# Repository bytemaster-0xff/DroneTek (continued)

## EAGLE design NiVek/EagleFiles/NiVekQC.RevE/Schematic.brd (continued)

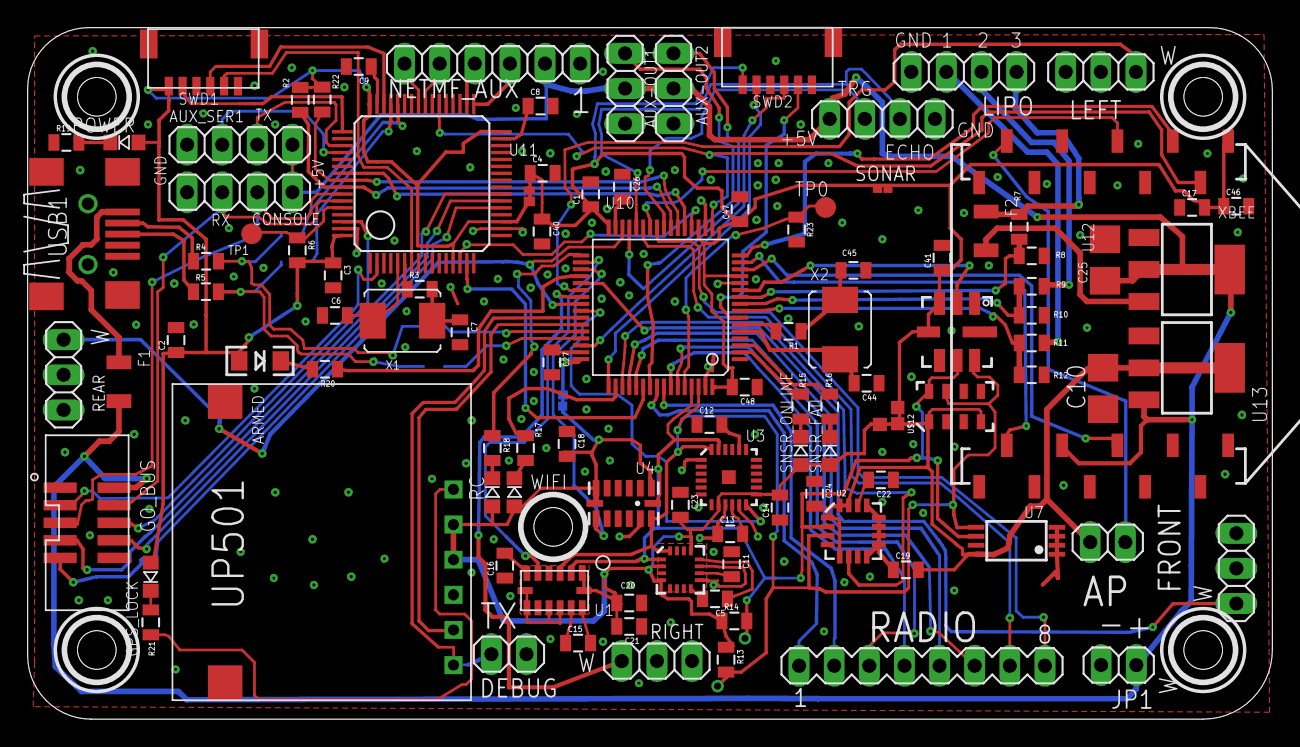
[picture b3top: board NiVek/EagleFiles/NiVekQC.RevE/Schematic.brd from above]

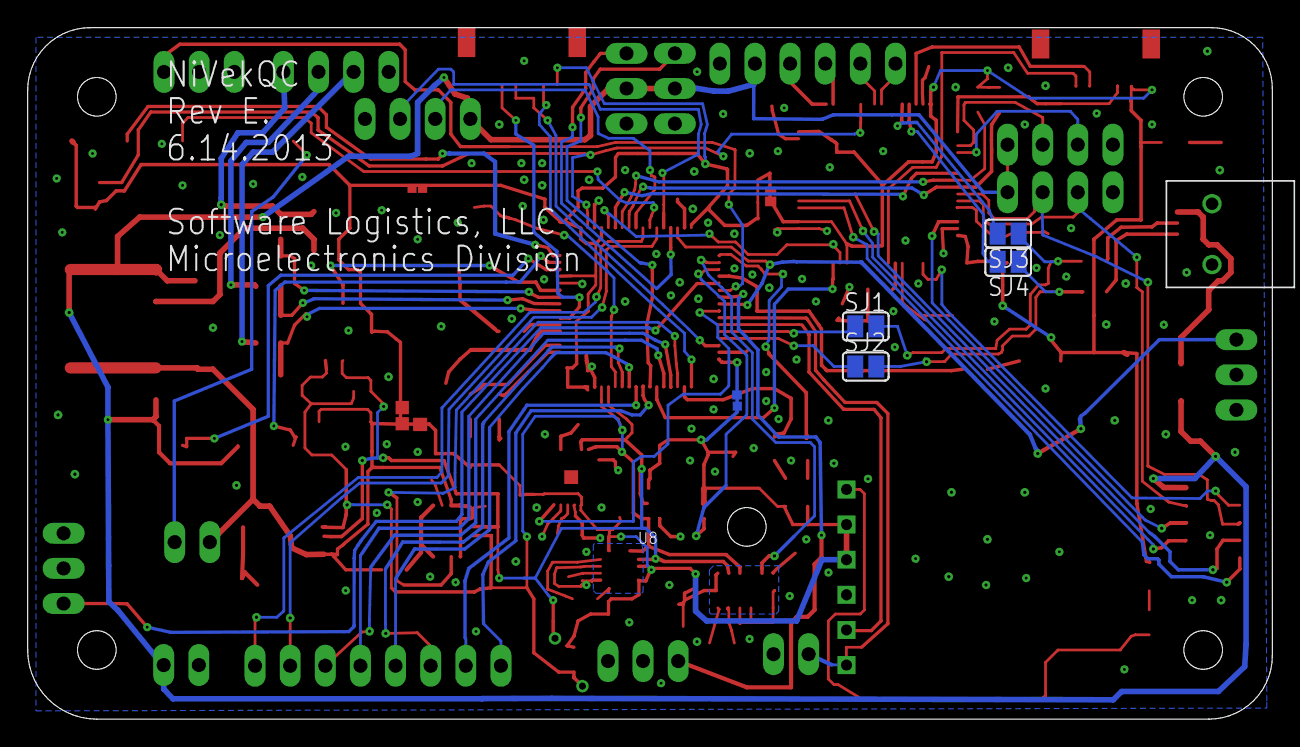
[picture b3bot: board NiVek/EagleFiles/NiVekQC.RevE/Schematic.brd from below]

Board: 2 copper layers, 90.0 x 50.0 mm, 107 parts (4 on the bottom side), 108 nets.

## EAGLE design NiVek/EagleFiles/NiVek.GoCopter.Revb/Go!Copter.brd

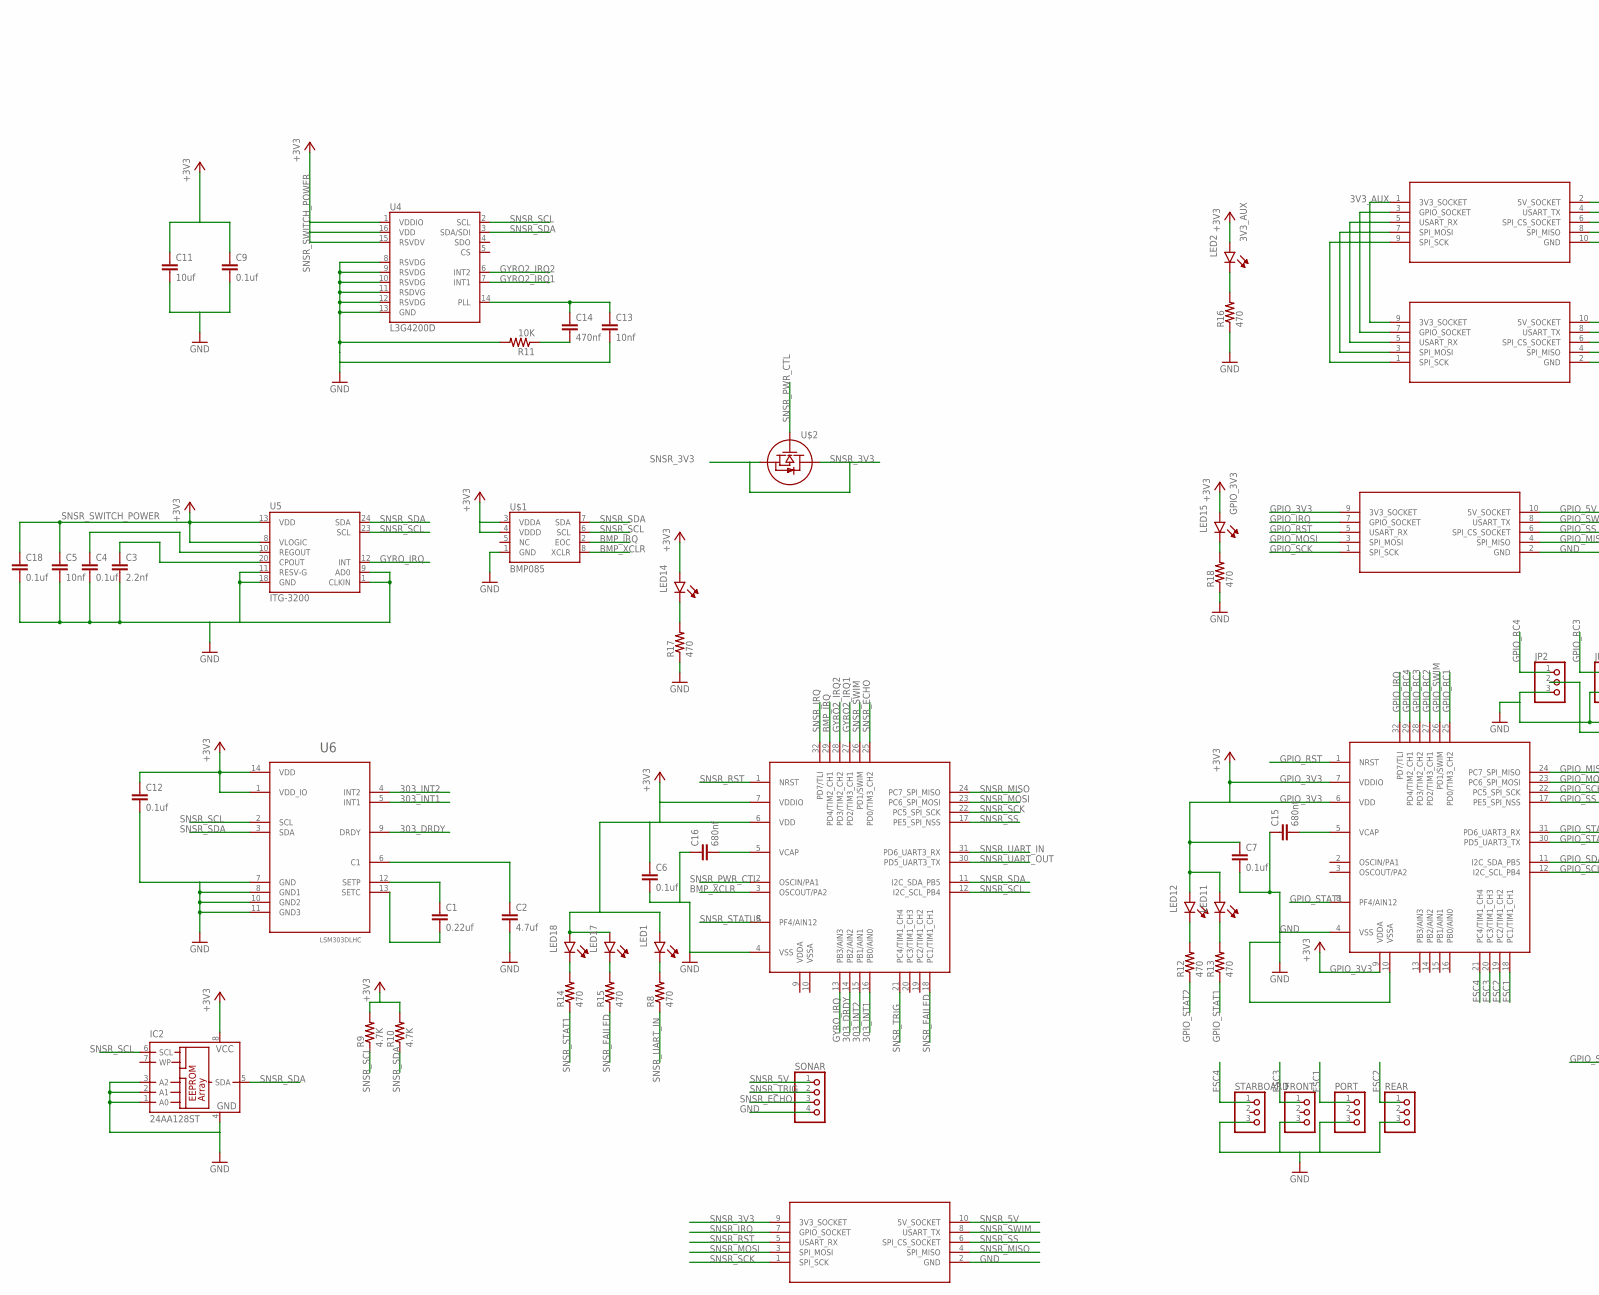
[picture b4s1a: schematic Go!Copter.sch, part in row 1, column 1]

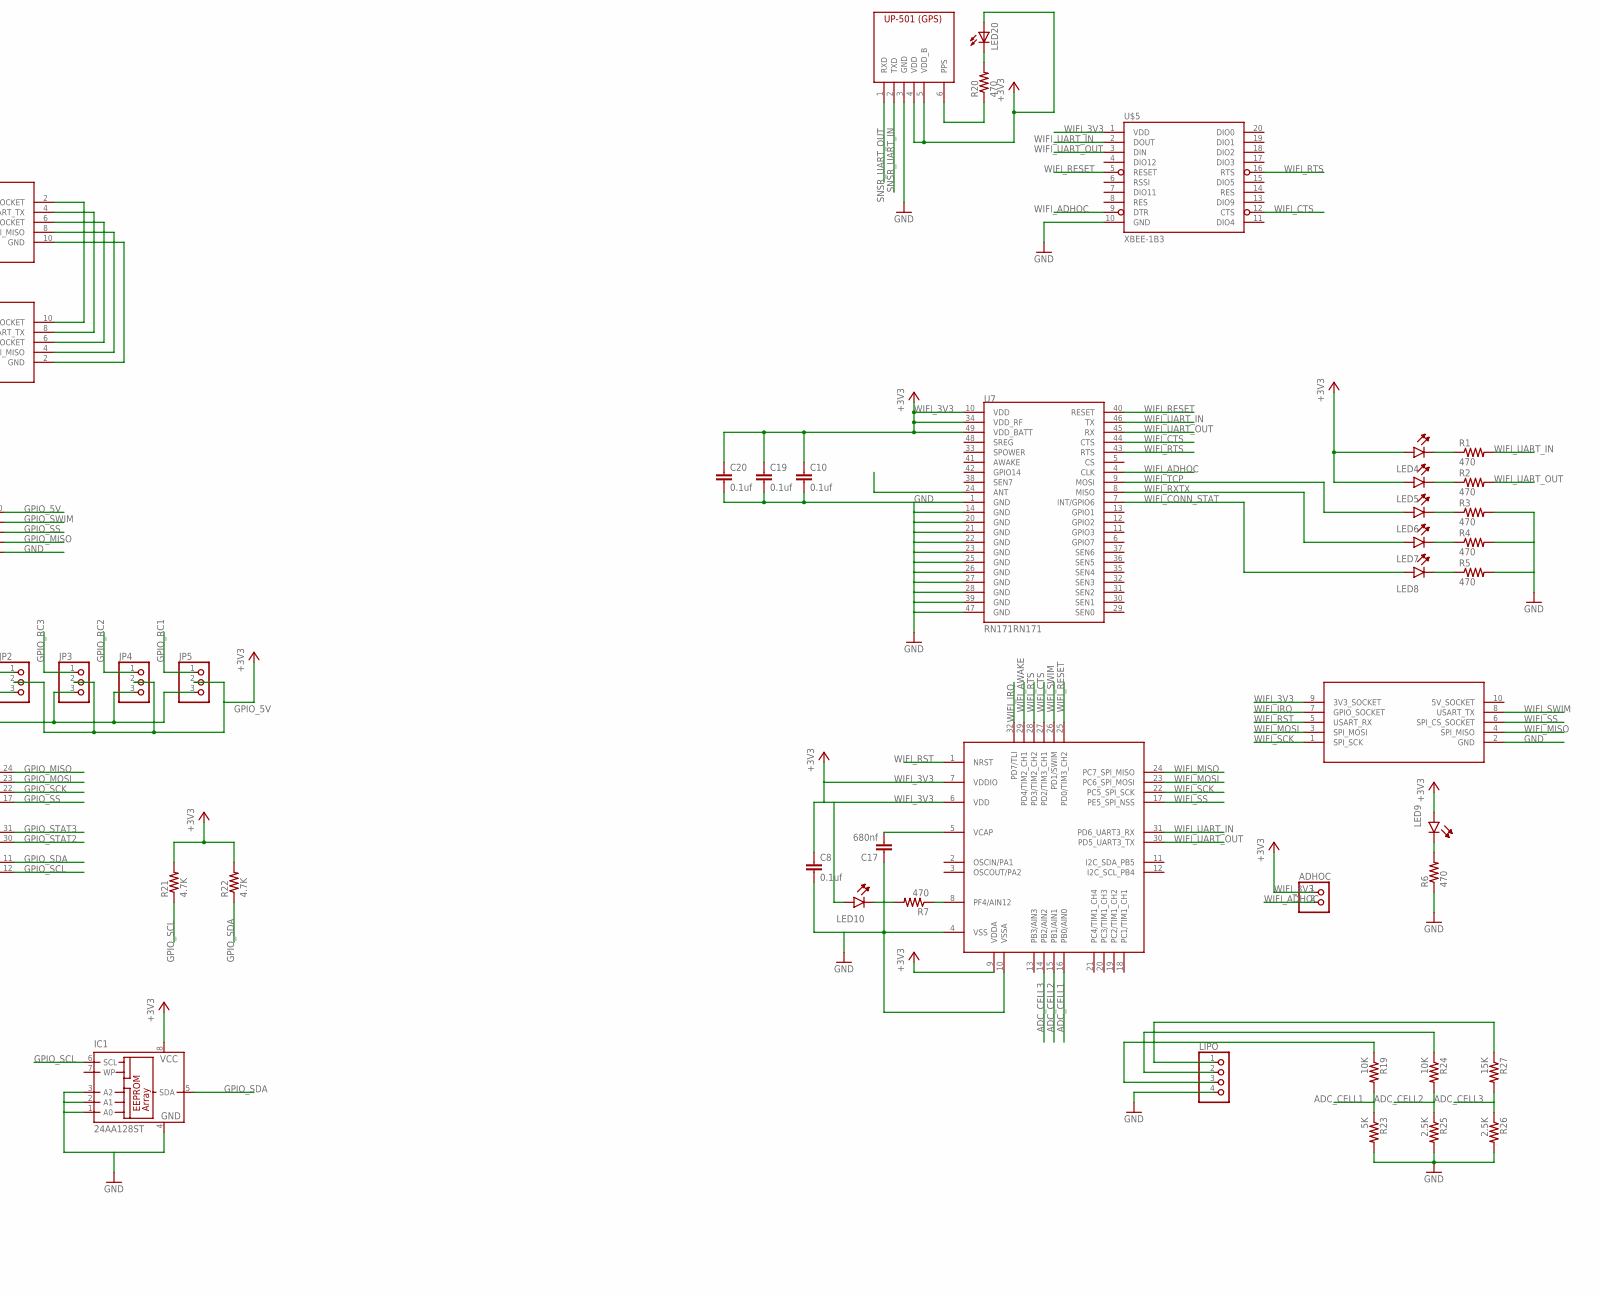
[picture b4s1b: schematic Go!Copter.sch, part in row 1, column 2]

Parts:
ADHOC: PINHD-1X2; 1X02
C1: 0.22uf; 0805
C2: 4.7uf; 0805
C3: 2.2nf; 0805
C4, C6, C7, C8, C9, C10, C12, C18, C19, C20: 0.1uf; 0805
C5, C13: 10nf; 0805
C11: 10uf; 0805
C14: 470nf; 0805
C15, C16, C17: 680nf; 0805
FRONT: PINHD-1X3; 1X03
IC1, IC2: 24AA128ST; TSSOP8; MPN 24AA128-I/ST
JP2, JP3, JP4, JP5: PINHD-1X3; 1X03
LED1, LED2, LED4, LED5, LED6, LED7, LED8, LED9, LED10, LED11, LED12, LED14, LED15, LED17, LED18: SMD_LED0805; LED0805
LED20: LEDCHIPLED_0805; CHIPLED_0805
LIPO: PINHD-1X4; 1X04
PORT: PINHD-1X3; 1X03
R1, R2, R3, R4, R5, R6, R7, R8, R12, R13, R14, R15, R16, R17, R18, R20: 470; 0805
R9, R10, R21, R22: 4.7K; 0805
R11, R19, R24: 10K; 0805
R23: 5K; 0805
R25, R26: 2.5K; 0805
R27: 15K; 0805
REAR: PINHD-1X3; 1X03
SONAR: PINHD-1X4; 1X04
STARBOARD: PINHD-1X3; 1X03
U1, U2, U3: STM8S207K6; LQFP32
U4: L3G4200D; LGA16-4X4
U5: ITG-3200; QFN-24
U6: LSM303DLHC; LGA3X5X1-14L
U7: RN171RN171; RN171
U$1: BMP085
U$2: MOSFET-BSS138; SOT-23
U$3, U$4, U$7, U$8: GO!BUS-FEMALE; PIN2ROW_0.05"
U$5: XBEE-1B3; XBEE-SMD
U$6: UP501; UP-501
U$9: GO!BUS; PIN2ROW_0.05"

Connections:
3V3_AUX: LED2.P$1 (A), U$8.9 (3V3_SOCKET), U$9.1 (3V3_SOCKET)
5V_AUX: U$8.10 (5V_SOCKET), U$9.2 (5V_SOCKET)
5V_SOCKET: U$4.10 (5V_SOCKET)
303_DRDY: U1.14 (PB2/AIN2), U6.9 (DRDY)
303_INT1: U1.16 (PB0/AIN0), U6.5 (INT1)
303_INT2: U1.15 (PB1/AIN1), U6.4 (INT2)
+3V3: U3.9 (VDDA)
ADC_CELL1: R19.2, R23.1, U3.16 (PB0/AIN0)
ADC_CELL2: R24.2, R25.1, U3.15 (PB1/AIN1)
ADC_CELL3: R26.1, R27.2, U3.14 (PB2/AIN2)
ANTENNA: U7.24 (ANT)
BMP_IRQ: U1.29 (PD4/TIM2_CH1), U$1.2 (EOC)
BMP_XCLR: U1.3 (OSCOUT/PA2), U$1.8 (XCLR)
ESC1: PORT.1, U2.18 (PC1/TIM1_CH1)
ESC2: REAR.1, U2.19 (PC2/TIM1_CH2)
ESC3: FRONT.1, U2.20 (PC3/TIM1_CH3)
ESC4: STARBOARD.1, U2.21 (PC4/TIM1_CH4)
GND: C2.2, C3.2, C4.2, C5.2, C6.2, C7.2, C8.2, C9.2, C10.2, C11.2, C12.2, C13.2, C15.1, C16.1, C17.1, C18.2, C19.2, C20.2, FRONT.3, IC1.1 (A0), IC1.2 (A1), IC1.3 (A2), IC1.4 (GND), IC2.1 (A0), IC2.2 (A1), IC2.3 (A2), IC2.4 (GND), JP2.3, JP3.3, JP4.3, JP5.3, LIPO.4, PORT.3, R3.2, R4.2, R5.2, R6.1, R11.2, R16.1, R17.1, R18.1, R23.2, R25.2, R26.2, REAR.3, SONAR.4, STARBOARD.3, U1.4 (VSS), U2.4 (VSS), U2.10 (VSSA), U3.4 (VSS), U3.10 (VSSA), U4.8 (RSVDG), U4.9 (RSVDG), U4.10 (RSVDG), U4.11 (RSDVG), U4.12 (RSVDG), U4.13 (GND), U5.1 (CLKIN), U5.9 (AD0), U5.11 (RESV-G), U5.18 (GND), U6.7 (GND), U6.8 (GND1), U6.10 (GND2), U6.11 (GND3), U7.1 (GND), U7.14 (GND), U7.20 (GND), U7.21 (GND), U7.22 (GND), U7.23 (GND), U7.25 (GND), U7.26 (GND), U7.27 (GND), U7.28 (GND), U7.39 (GND), U7.47 (GND), U$1.1 (GND), U$3.2 (GND), U$4.2 (GND), U$5.10 (GND), U$6.3 (GND), U$7.2 (GND), U$8.2 (GND), U$9.10 (GND)
GPIO_3V3: C7.1, IC1.8 (VCC), LED11.P$1 (A), LED12.P$1 (A), LED15.P$1 (A), R21.2, R22.2, U2.6 (VDD), U2.7 (VDDIO), U2.9 (VDDA), U$3.9 (3V3_SOCKET)
GPIO_5V: JP2.2, JP3.2, JP4.2, JP5.2, U$3.10 (5V_SOCKET)
GPIO_IRQ: U2.32 (PD7/TLI), U$3.7 (GPIO_SOCKET)
GPIO_MISO: U2.24 (PC7_SPI_MISO), U$3.4 (SPI_MISO)
GPIO_MOSI: U2.23 (PC6_SPI_MOSI), U$3.3 (SPI_MOSI)
GPIO_RC1: JP5.1, U2.25 (PD0/TIM3_CH2)
GPIO_RC2: JP4.1, U2.27 (PD2/TIM3_CH1)
GPIO_RC3: JP3.1, U2.28 (PD3/TIM2_CH2)
GPIO_RC4: JP2.1, U2.29 (PD4/TIM2_CH1)
GPIO_RST: U2.1 (NRST), U$3.5 (USART_RX)
GPIO_SCK: U2.22 (PC5_SPI_SCK), U$3.1 (SPI_SCK)
GPIO_SCL: IC1.6 (SCL), R21.1, U2.12 (I2C_SCL_PB4)
GPIO_SDA: IC1.5 (SDA), R22.1, U2.11 (I2C_SDA_PB5)
GPIO_SS: U2.17 (PE5_SPI_NSS), U$3.6 (SPI_CS_SOCKET)
GPIO_STAT1: R13.1, U2.8 (PF4/AIN12)
GPIO_STAT2: R12.1, U2.30 (PD5_UART3_TX)
GPIO_STAT3: U2.31 (PD6_UART3_RX)
GPIO_SWIM: U2.26 (PD1/SWIM), U$3.8 (USART_TX)
GYRO2_IRQ1: U1.27 (PD2/TIM3_CH1), U4.7 (INT1)
GYRO2_IRQ2: U1.28 (PD3/TIM2_CH2), U4.6 (INT2)
GYRO_IRQ: U1.13 (PB3/AIN3), U5.12 (INT)
unnamed: LED18.C, R14.2
unnamed: LED1.C, R8.2
unnamed: C4.1, U5.10 (REGOUT)
unnamed: C3.1, U5.20 (CPOUT)
unnamed: LED4.C, R1.1
unnamed: C1.1, U6.12 (SETP)
unnamed: C1.2, U6.13 (SETC)
unnamed: C2.1, U6.6 (C1)
unnamed: LED5.C, R2.1
unnamed: LED6.C, R3.1
unnamed: LED7.C, R4.1
unnamed: LED8.C, R5.1
unnamed: LED9.C, R6.2
unnamed: LED10.C, R7.2
unnamed: R7.1, U3.8 (PF4/AIN12)
unnamed: LED17.C, R15.2
unnamed: LED15.C, R18.2
unnamed: LED2.C, R16.2
unnamed: LED12.C, R12.2
unnamed: LED11.C, R13.2
unnamed: U$8.7 (GPIO_SOCKET), U$9.3 (GPIO_SOCKET)
unnamed: LED14.C, R17.2
unnamed: U$8.5 (USART_RX), U$9.5 (USART_RX)
unnamed: U$8.3 (SPI_MOSI), U$9.7 (SPI_MOSI)
unnamed: R20.1, U$6.6 (PPS)
unnamed: C15.2, U2.5 (VCAP)
unnamed: U$8.1 (SPI_SCK), U$9.9 (SPI_SCK)
unnamed: LED20.C, R20.2
unnamed: C16.2, U1.5 (VCAP)
unnamed: C17.2, U3.5 (VCAP)
unnamed: C14.2, R11.1
unnamed: U$8.8 (USART_TX), U$9.4 (USART_TX)
unnamed: U$8.6 (SPI_CS_SOCKET), U$9.6 (SPI_CS_SOCKET)
unnamed: U$8.4 (SPI_MISO), U$9.8 (SPI_MISO)
unnamed: C13.1, C14.1, U4.14 (PLL)
unnamed: LIPO.3, R19.1
unnamed: LIPO.2, R24.1
unnamed: LIPO.1, R27.1
SNSR_3V3: C6.1, IC2.8 (VCC), LED1.P$1 (A), LED14.P$1 (A), LED17.P$1 (A), LED18.P$1 (A), LED20.A, R9.2, R10.2, U1.6 (VDD), U1.7 (VDDIO), U$2.BOTTOM_RIGHT (S), U$2.TOP (D), U$6.4 (VDD), U$6.5 (VDD_B), U$7.9 (3V3_SOCKET)
SNSR_5V: SONAR.1, U$7.10 (5V_SOCKET)
SNSR_ECHO: SONAR.3, U1.25 (PD0/TIM3_CH2)
SNSR_FAILED: R15.1, U1.18 (PC1/TIM1_CH1)
SNSR_IRQ: U1.32 (PD7/TLI), U$7.7 (GPIO_SOCKET)
SNSR_MISO: U1.24 (PC7_SPI_MISO), U$7.4 (SPI_MISO)
SNSR_MOSI: U1.23 (PC6_SPI_MOSI), U$7.3 (SPI_MOSI)
SNSR_PWR_CTL: U1.2 (OSCIN/PA1), U$2.BOTTOM_LEFT (G)
SNSR_RST: U1.1 (NRST), U$7.5 (USART_RX)
SNSR_SCK: U1.22 (PC5_SPI_SCK), U$7.1 (SPI_SCK)
SNSR_SCL: IC2.6 (SCL), R9.1, U1.12 (I2C_SCL_PB4), U4.2 (SCL), U5.23 (SCL), U6.2 (SCL), U$1.6 (SCL)
SNSR_SDA: IC2.5 (SDA), R10.1, U1.11 (I2C_SDA_PB5), U4.3 (SDA/SDI), U5.24 (SDA), U6.3 (SDA), U$1.7 (SDA)
SNSR_SS: U1.17 (PE5_SPI_NSS), U$7.6 (SPI_CS_SOCKET)
SNSR_STAT1: R14.1
SNSR_STATUS: U1.8 (PF4/AIN12)
SNSR_SWIM: U1.26 (PD1/SWIM), U$7.8 (USART_TX)
SNSR_SWITCH_POWER: C5.1, C9.1, C11.1, C12.1, C18.1, U4.1 (VDDIO), U4.15 (RSVDV), U4.16 (VDD), U5.8 (VLOGIC), U5.13 (VDD), U6.1 (VDD_IO), U6.14 (VDD), U$1.3 (VDDA), U$1.4 (VDDD)
SNSR_TRIG: SONAR.2, U1.21 (PC4/TIM1_CH4)
SNSR_UART_IN: R8.1, U1.31 (PD6_UART3_RX), U$6.2 (TXD)
SNSR_UART_OUT: U1.30 (PD5_UART3_TX), U$6.1 (RXD)
WIFI_3V3: ADHOC.1, C8.1, C10.1, C19.1, C20.1, LED4.P$1 (A), LED5.P$1 (A), LED9.P$1 (A), LED10.P$1 (A), U3.6 (VDD), U3.7 (VDDIO), U7.10 (VDD), U7.34 (VDD_RF), U7.49 (VDD_BATT), U$4.9 (3V3_SOCKET), U$5.1 (VDD)
WIFI_ADHOC: ADHOC.2, U7.4 (CLK), U$5.9 (DTR)
WIFI_AWAKE: U3.29 (PD4/TIM2_CH1)
WIFI_CONN_STAT: LED8.P$1 (A), U7.7 (INT/GPIO6)
WIFI_CTS: U3.27 (PD2/TIM3_CH1), U7.44 (CTS), U$5.12 (CTS)
WIFI_IRQ: U3.32 (PD7/TLI), U$4.7 (GPIO_SOCKET)
WIFI_MISO: U3.24 (PC7_SPI_MISO), U$4.4 (SPI_MISO)
WIFI_MOSI: U3.23 (PC6_SPI_MOSI), U$4.3 (SPI_MOSI)
WIFI_RESET: U3.25 (PD0/TIM3_CH2), U7.40 (RESET), U$5.5 (RESET)
WIFI_RST: U3.1 (NRST), U$4.5 (USART_RX)
WIFI_RTS: U3.28 (PD3/TIM2_CH2), U7.43 (RTS), U$5.16 (RTS)
WIFI_RXTX: LED7.P$1 (A), U7.8 (MISO)
WIFI_SCK: U3.22 (PC5_SPI_SCK), U$4.1 (SPI_SCK)
WIFI_SS: U3.17 (PE5_SPI_NSS), U$4.6 (SPI_CS_SOCKET)
WIFI_SWIM: U3.26 (PD1/SWIM), U$4.8 (USART_TX)
WIFI_TCP: LED6.P$1 (A), U7.9 (MOSI)
WIFI_UART_IN: R1.2, U3.31 (PD6_UART3_RX), U7.46 (TX), U$5.2 (DOUT)
WIFI_UART_OUT: R2.2, U3.30 (PD5_UART3_TX), U7.45 (RX), U$5.3 (DIN)

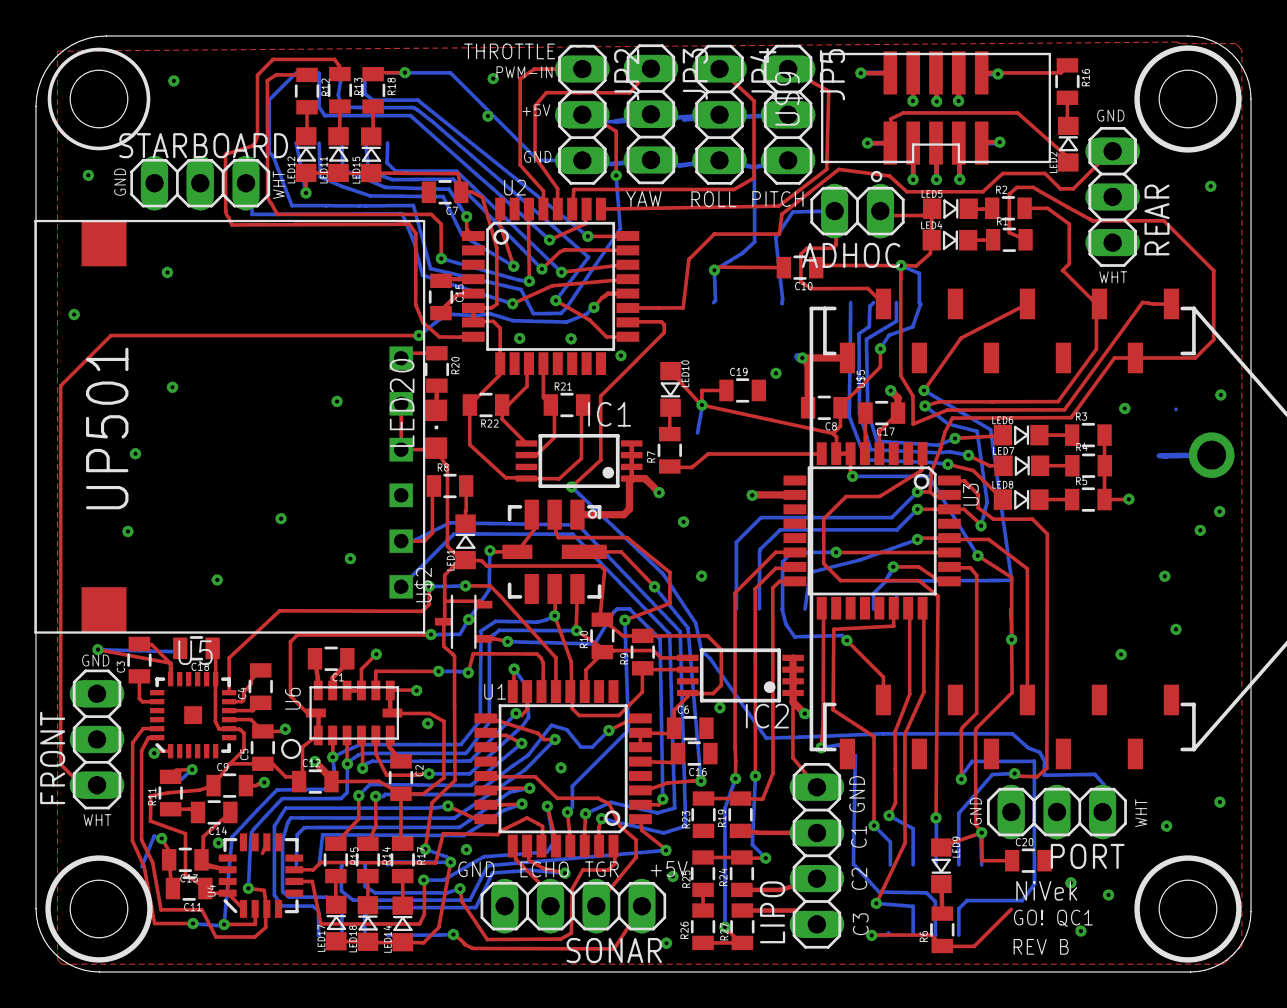
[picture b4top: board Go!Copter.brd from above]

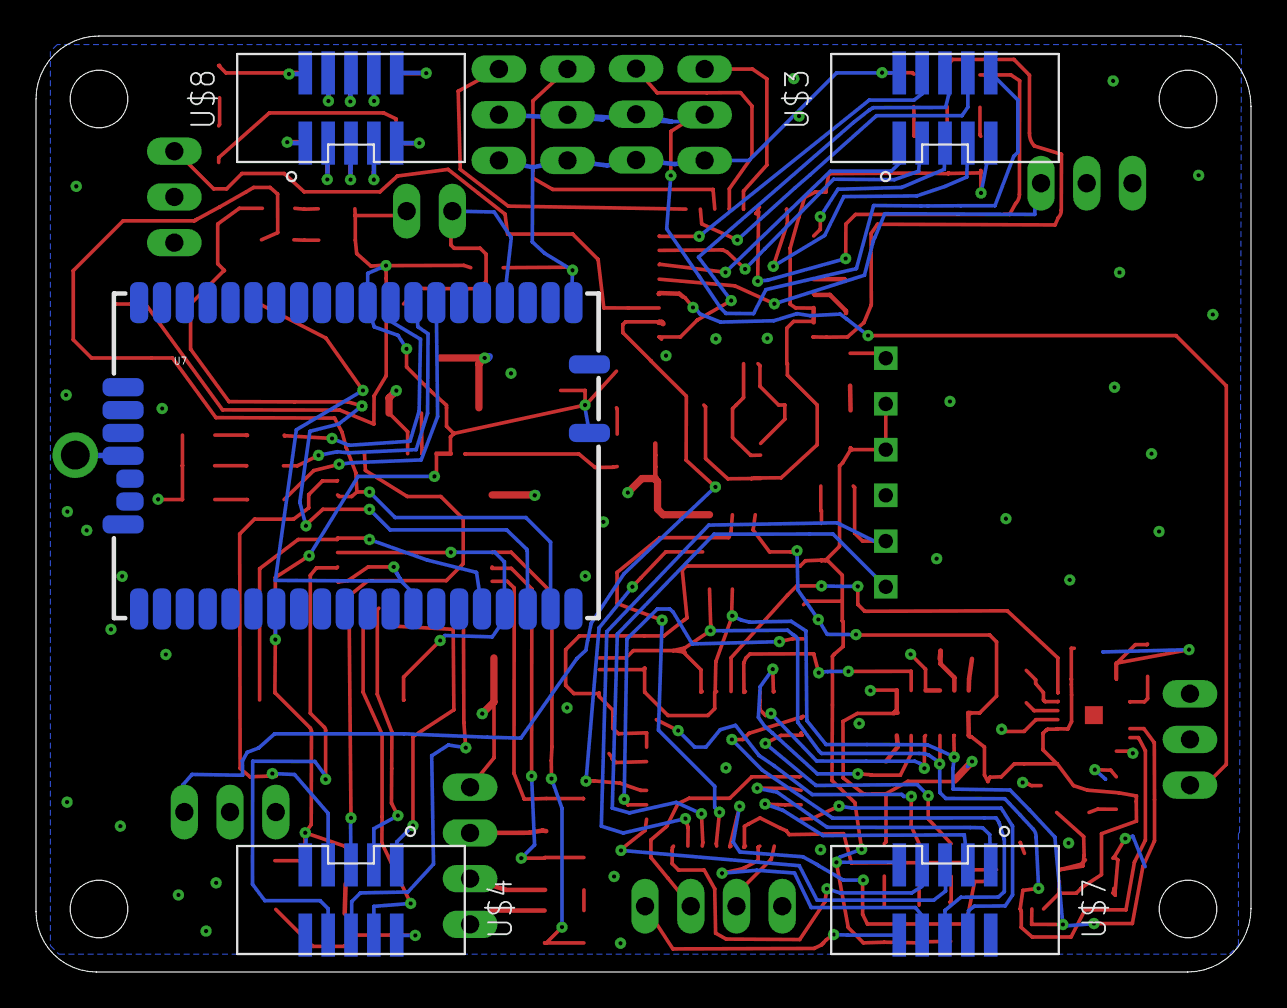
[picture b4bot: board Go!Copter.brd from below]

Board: 2 copper layers, 67.5 x 52.0 mm, 92 parts (5 on the bottom side), 108 nets.

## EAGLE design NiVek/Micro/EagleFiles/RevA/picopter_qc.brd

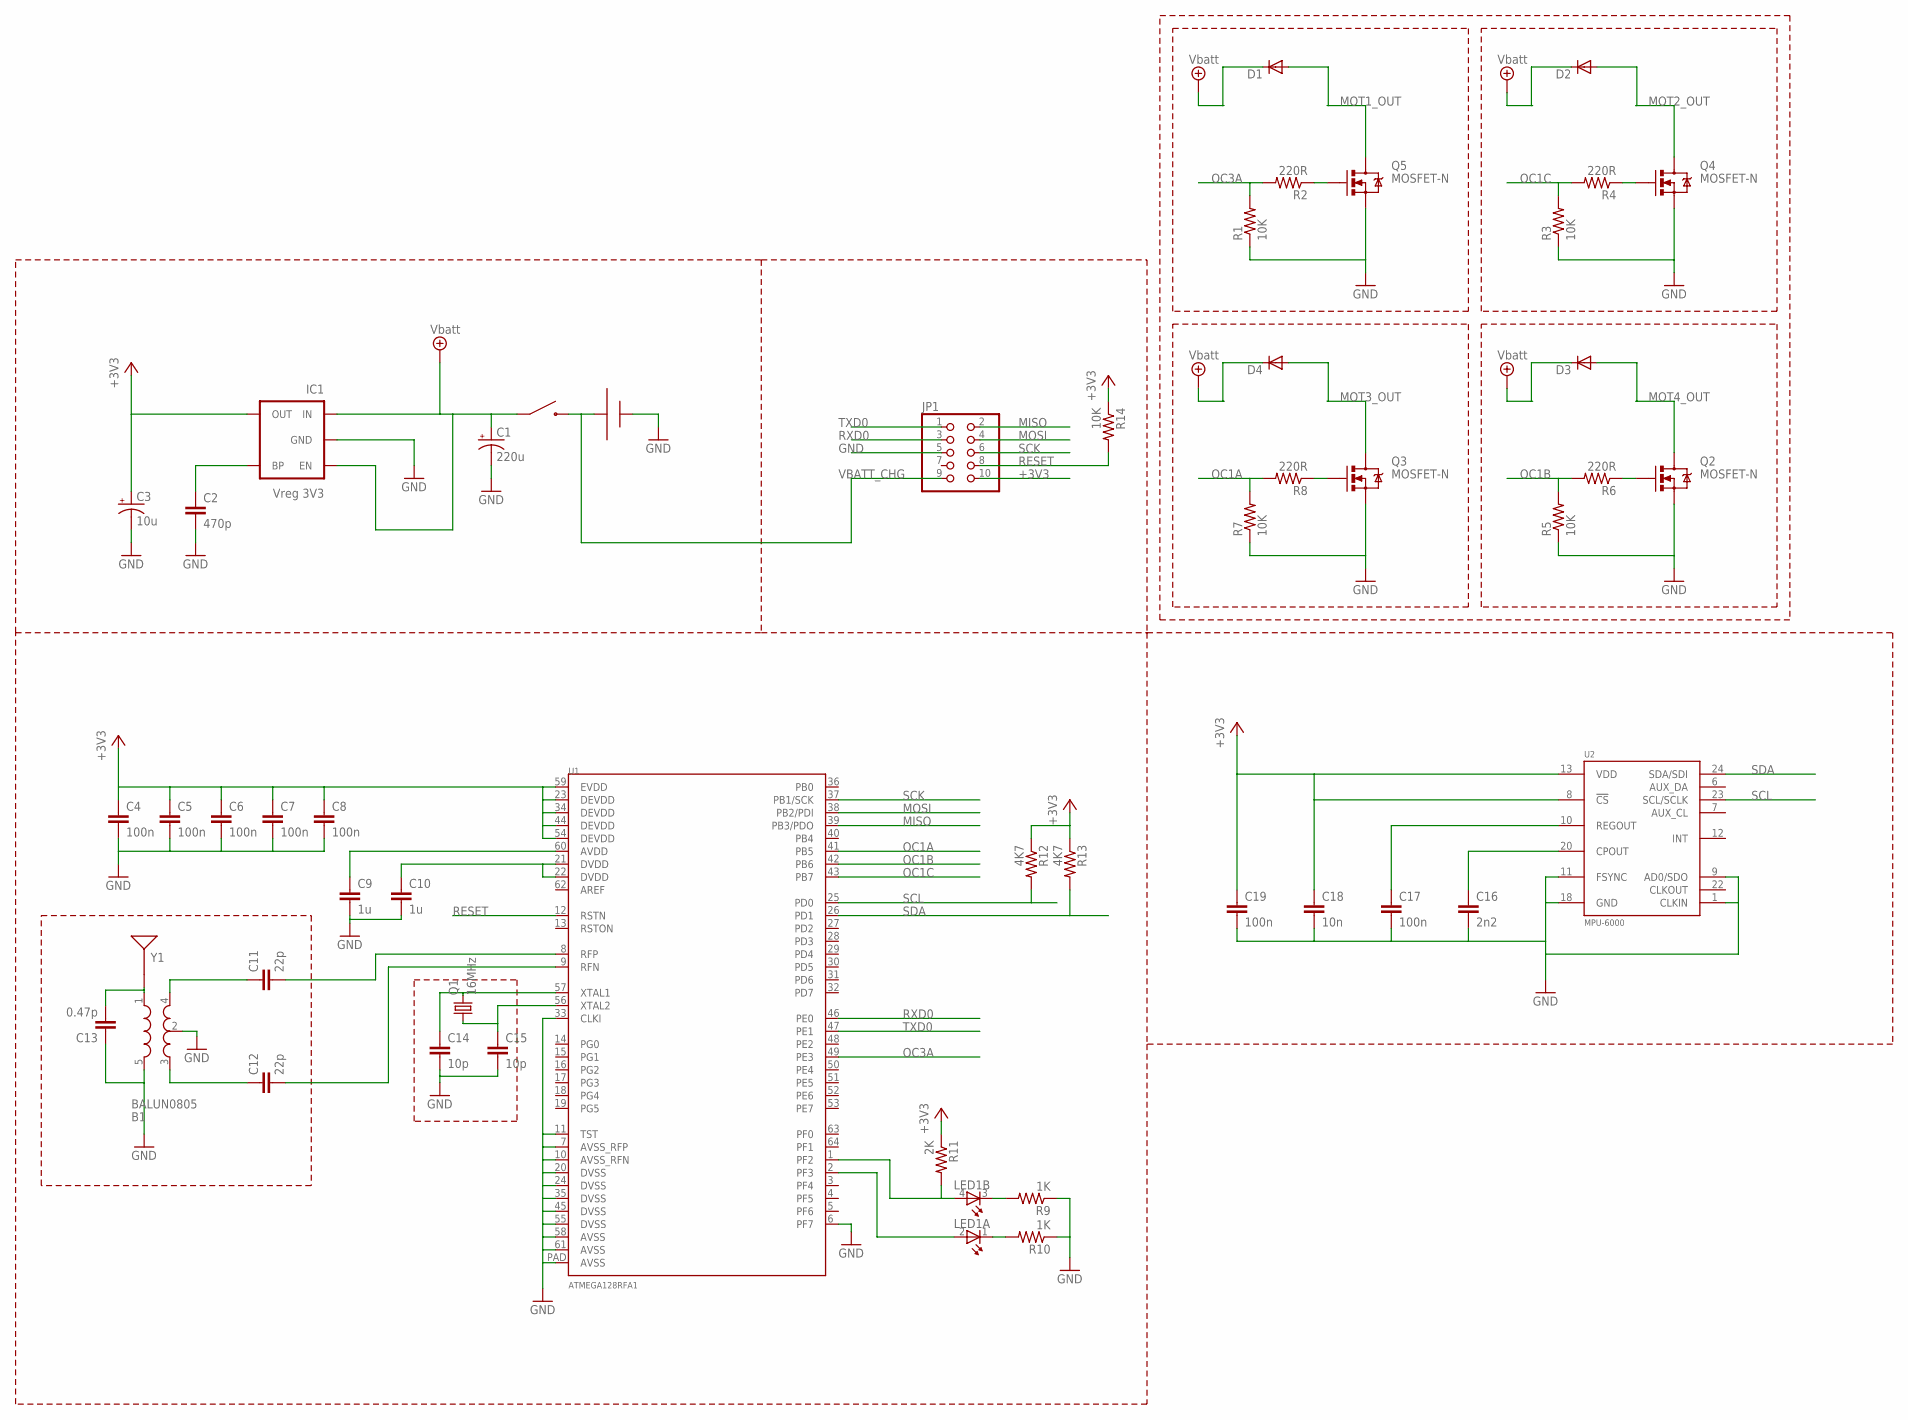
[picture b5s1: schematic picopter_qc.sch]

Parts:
B1: BALUN0805; BALUN
BATT1: BATT-CONNJST-PH-VERT; JST-PH-2-VERT
C1: 220u; SMC_B
C2: 470p; C0603
C3: 10u; SMC_B
C4, C5, C6, C7, C8, C17, C19: 100n; C0603
C9, C10: 1u; C0603
C11, C12: 22p; C0603
C13: 0.47p; C0603
C14, C15: 10p; C0603
C16: 2n2; C0603
C18: 10n; C0603
D1, D2, D3, D4: DIODE-MINIMELF; MINIMELF
IC1: Vreg 3V3; SOT23-5
JP1: PINHD-2X5EDGE; 2X5-EDGE
LED1: TOPLED-2-CUSTOM; TOPLED2CUSTOM
Q1: 16MHz; CTS406
Q2, Q3, Q4, Q5: MOSFET-N; SOT23-3
R1, R3, R5, R7, R14: 10K; R0603
R2, R4, R6, R8: 220R; R0603
R9, R10: 1K; R0603
R11: 2K; R0603
R12, R13: 4K7; R0603
S2: SWITCH-PWR-SIMPLE; SWITCH-PWR
U1: ATMEGA128RFA1; QFN-64
U2: MPU-6000; QFN-24
Y1: ANTENNA2SMD5; ANTENNA-CHIP5

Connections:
+3V3: C3.+, C4.1, C5.1, C6.1, C7.1, C8.1, C18.1, C19.1, IC1.5 (OUT), JP1.10, R11.1, R12.1, R13.1, R14.1, U1.23 (DEVDD), U1.34 (DEVDD), U1.44 (DEVDD), U1.54 (DEVDD), U1.59 (EVDD), U2.8 (!CS), U2.13 (VDD)
GND: B1.2 (GND), B1.5 (GND), BATT1.N, C1.-, C2.2, C3.-, C4.2, C5.2, C6.2, C7.2, C8.2, C9.2, C10.2, C13.1, C14.2, C15.2, C16.2, C17.2, C18.2, C19.2, IC1.2 (GND), JP1.5, Q2.2 (S), Q3.2 (S), Q4.2 (S), Q5.2 (S), R1.1, R3.1, R5.1, R7.1, R9.1, R10.1, U1.6 (PF7), U1.7 (AVSS_RFP), U1.10 (AVSS_RFN), U1.11 (TST), U1.20 (DVSS), U1.24 (DVSS), U1.33 (CLKI), U1.35 (DVSS), U1.45 (DVSS), U1.55 (DVSS), U1.58 (AVSS), U1.61 (AVSS), U1.PAD (AVSS), U2.1 (CLKIN), U2.9 (AD0/SDO), U2.11 (FSYNC), U2.18 (GND)
MISO: JP1.2, U1.39 (PB3/PDO)
MOSI: JP1.4, U1.38 (PB2/PDI)
MOT1_OUT: D1.A, Q5.3 (D)
MOT2_OUT: D2.A, Q4.3 (D)
MOT3_OUT: D4.A, Q3.3 (D)
MOT4_OUT: D3.A, Q2.3 (D)
MS1: B1.1 (IN), C13.2, Y1.FEED
unnamed: C2.1, IC1.4 (BP)
unnamed: LED1.4 (A), R11.2, U1.1 (PF2)
unnamed: C11.2, U1.8 (RFP)
unnamed: C10.1, U1.21 (DVDD), U1.22 (DVDD)
unnamed: C9.1, U1.60 (AVDD)
unnamed: B1.3 (OUT1), C12.1
unnamed: B1.4 (OUT2), C11.1
unnamed: C12.2, U1.9 (RFN)
unnamed: C14.1, Q1.3 (2), U1.57 (XTAL1)
unnamed: C15.1, Q1.1, U1.56 (XTAL2)
unnamed: LED1.3 (C), R9.2
unnamed: LED1.1 (C), R10.2
unnamed: LED1.2 (A), U1.2 (PF3)
unnamed: C16.1, U2.20 (CPOUT)
unnamed: C17.1, U2.10 (REGOUT)
unnamed: Q5.1 (G), R2.1
unnamed: Q4.1 (G), R4.1
unnamed: Q2.1 (G), R6.1
unnamed: Q3.1 (G), R8.1
OC1A: R7.2, R8.2, U1.41 (PB5)
OC1B: R5.2, R6.2, U1.42 (PB6)
OC1C: R3.2, R4.2, U1.43 (PB7)
OC3A: R1.2, R2.2, U1.49 (PE3)
RESET: JP1.8, R14.2, U1.12 (RSTN)
RXD0: JP1.3, U1.46 (PE0)
SCK: JP1.6, U1.37 (PB1/SCK)
SCL: R12.2, U1.25 (PD0), U2.23 (SCL/SCLK)
SDA: R13.2, U1.26 (PD1), U2.24 (SDA/SDI)
TXD0: JP1.1, U1.47 (PE1)
VBATT: C1.+, D1.C, D2.C, D3.C, D4.C, IC1.1 (IN), IC1.3 (EN), S2.P$1
VBATT_CHG: BATT1.P, JP1.9, S2.P$2

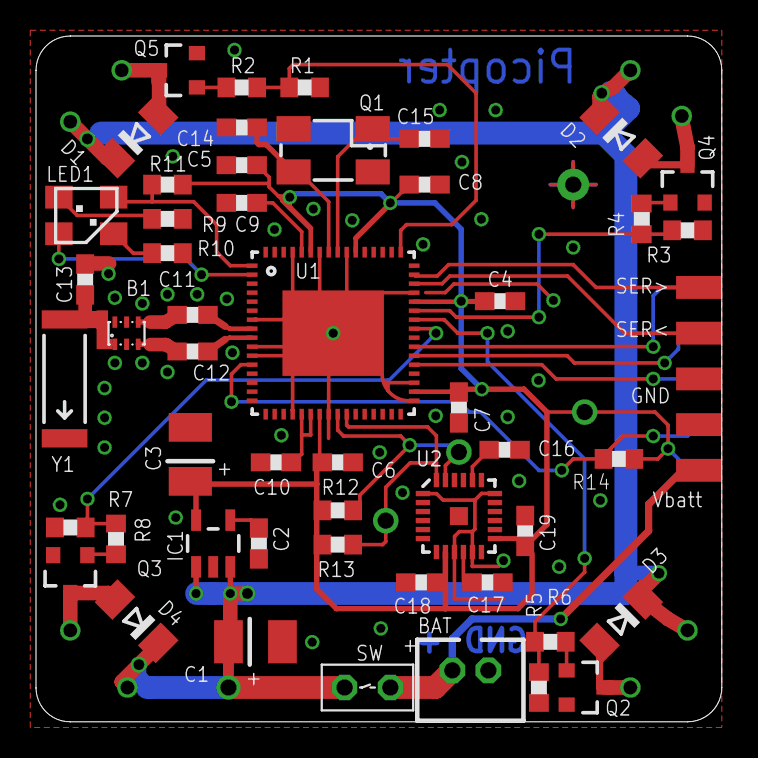
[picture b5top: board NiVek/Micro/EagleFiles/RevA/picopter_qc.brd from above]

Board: 2 copper layers, 38.1 x 38.1 mm, 56 parts (1 on the bottom side), 40 nets.

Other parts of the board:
U$1: PICOPTER-LOGO
U$5, U$6, U$7, U$8: ARM-MOCK

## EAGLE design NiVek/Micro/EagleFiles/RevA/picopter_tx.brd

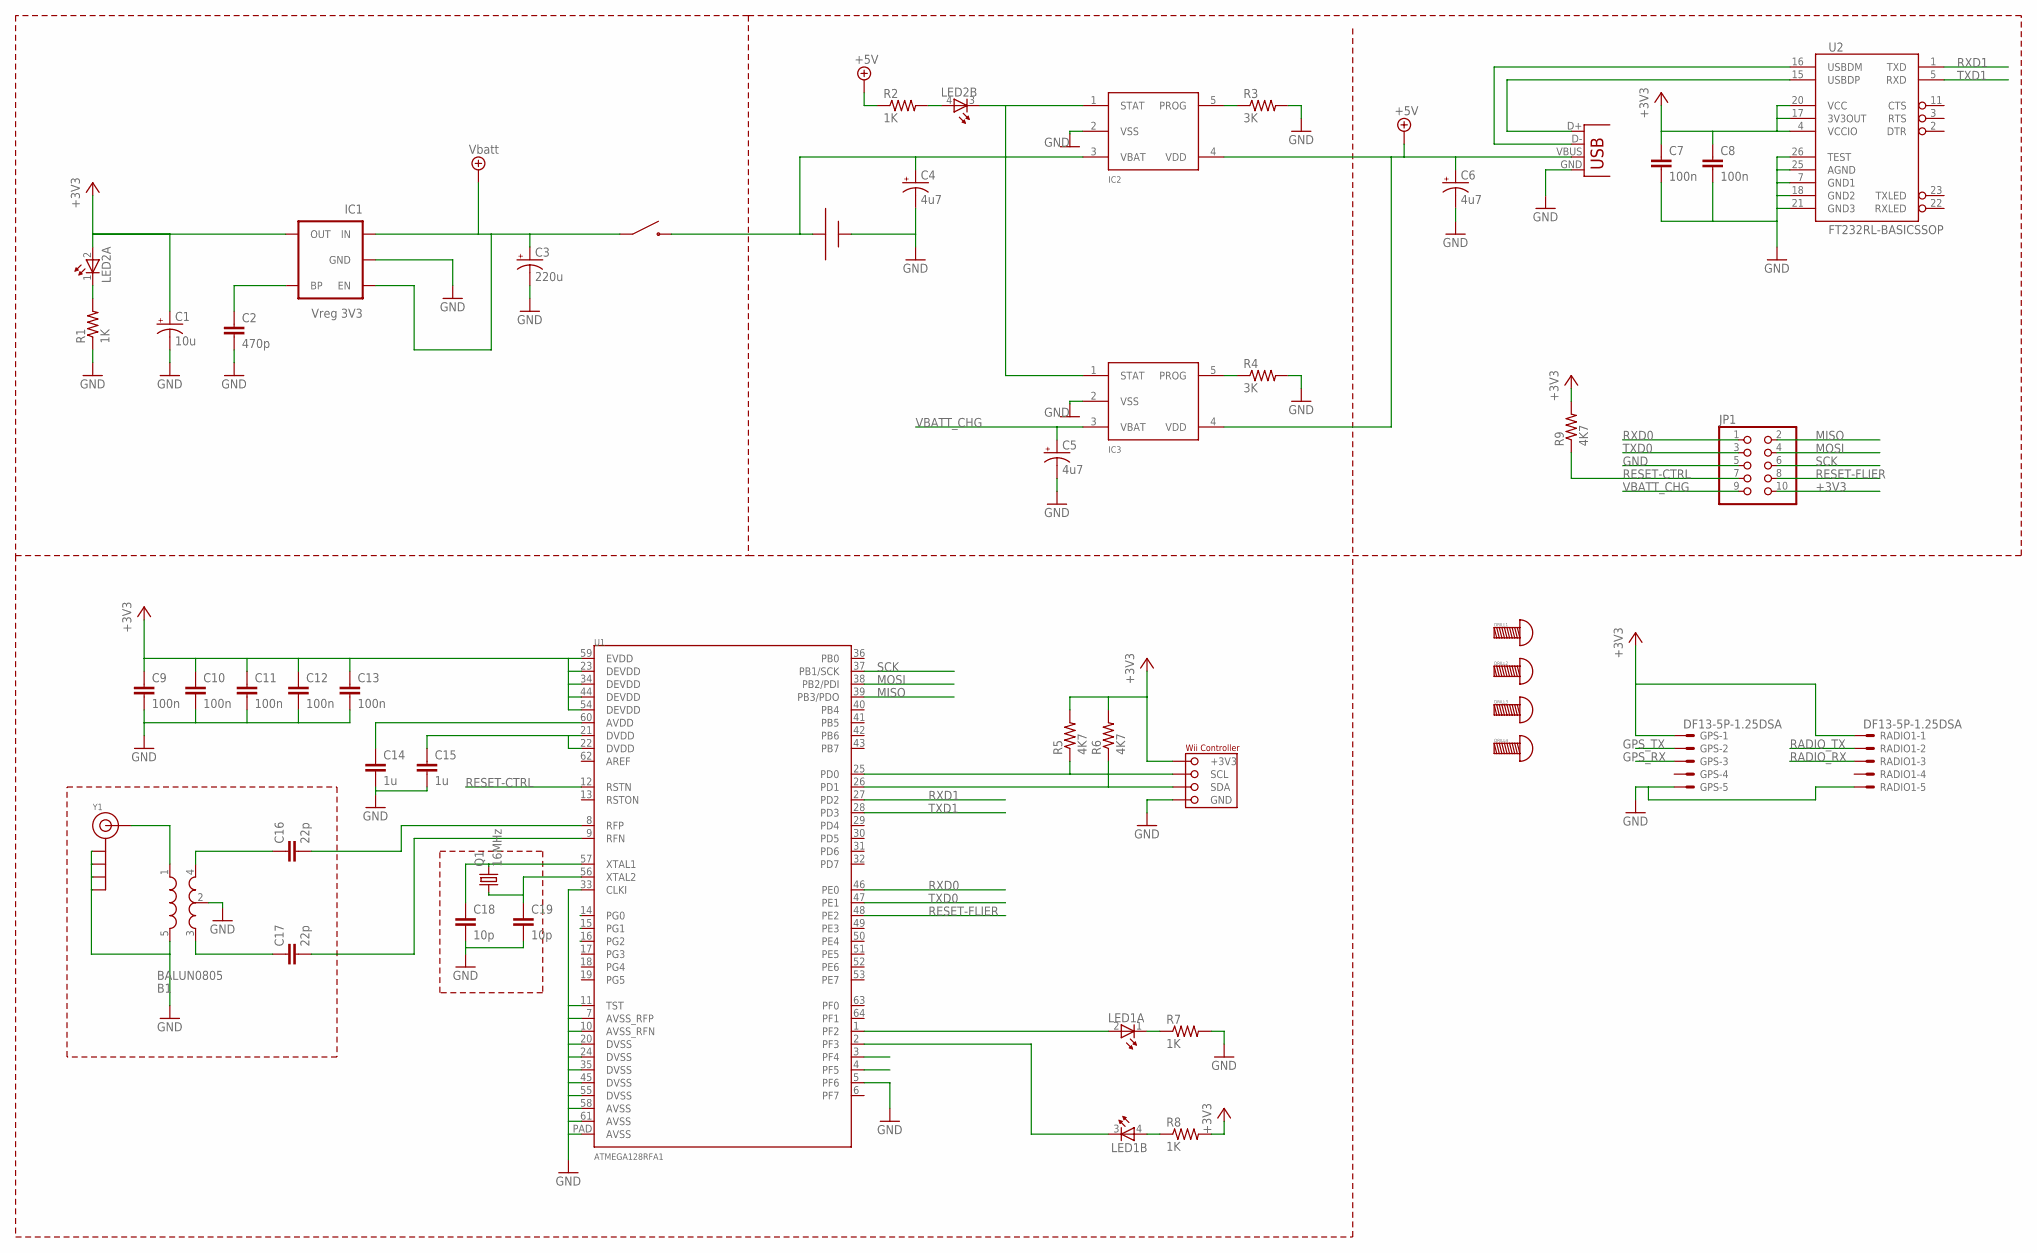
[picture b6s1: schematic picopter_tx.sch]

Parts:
B1: BALUN0805; BALUN
BATT2: BATT-CONNJST-PH-90; JST-PH-2-90
C1: 10u; SMC_B
C2: 470p; C0603
C3: 220u; SMC_B
C4, C5, C6: 4u7; SMC_B
C7, C8, C9, C10, C11, C12, C13: 100n; C0603
C14, C15: 1u; C0603
C16, C17: 22p; C0603
C18, C19: 10p; C0603
DRILL1, DRILL2, DRILL3, DRILL4: HOLE-4-40
GPS: DF13-5P-1.25DSA
IC1: Vreg 3V3; SOT23-5
IC2, IC3: MCP-LI-CHARGER-1; SOT23-5
JP1: PINHD-2X5EDGE; 2X5-EDGE
LED1, LED2: TOPLED-2-CUSTOM; TOPLED2CUSTOM
Q1: 16MHz; CTS406
R1, R2, R7, R8: 1K; R0603
R3, R4: 3K; R0603
R5, R6, R9: 4K7; R0603
RADIO1: DF13-5P-1.25DSA
S1: SWITCH-PWR-CNKOS2; SWITCH-SPDT-CNK-OS2
U1: ATMEGA128RFA1; QFN-64
U2: FT232RL-BASICSSOP; SSOP28DB
USB: USB-SMD-NS; USB-MINIB-NOSTOP
X11: WII-CONN; WII-CONN-2
Y1: SMA_EDGE; SMA-EDGE

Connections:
+3V3: C1.+, C7.1, C8.1, C9.1, C10.1, C11.1, C12.1, C13.1, GPS.1, IC1.5 (OUT), JP1.10, LED2.2 (A), R5.2, R6.2, R8.2, R9.2, RADIO1.1, U1.23 (DEVDD), U1.34 (DEVDD), U1.44 (DEVDD), U1.54 (DEVDD), U1.59 (EVDD), U2.4 (VCCIO), U2.17 (3V3OUT), U2.20 (VCC), X11.+3V3
GND: B1.2 (GND), B1.5 (GND), BATT2.N, C1.-, C2.2, C3.-, C4.-, C5.-, C6.-, C7.2, C8.2, C9.2, C10.2, C11.2, C12.2, C13.2, C14.2, C15.2, C18.2, C19.2, GPS.5, IC1.2 (GND), IC2.2 (VSS), IC3.2 (VSS), JP1.5, R1.1, R3.2, R4.2, R7.2, RADIO1.5, U1.5 (PF6), U1.7 (AVSS_RFP), U1.10 (AVSS_RFN), U1.11 (TST), U1.20 (DVSS), U1.24 (DVSS), U1.33 (CLKI), U1.35 (DVSS), U1.45 (DVSS), U1.55 (DVSS), U1.58 (AVSS), U1.61 (AVSS), U1.PAD (AVSS), U2.7 (GND1), U2.18 (GND2), U2.21 (GND3), U2.25 (AGND), U2.26 (TEST), USB.GND, X11.GND, Y1.GND@0 (GND), Y1.GND@1 (GND), Y1.GND@2 (GND), Y1.GND@3 (GND)
GPS_RX: GPS.3
GPS_TX: GPS.2
MISO: JP1.2, U1.39 (PB3/PDO)
MOSI: JP1.4, U1.38 (PB2/PDI)
unnamed: LED1.2 (A), U1.1 (PF2)
unnamed: LED1.1 (C), R7.1
unnamed: LED1.4 (A), R8.1
unnamed: LED2.4 (A), R2.2
unnamed: LED2.1 (C), R1.2
unnamed: IC2.5 (PROG), R3.1
unnamed: IC3.5 (PROG), R4.1
unnamed: U2.16 (USBDM), USB.D-
unnamed: U2.15 (USBDP), USB.D+
unnamed: C2.1, IC1.4 (BP)
unnamed: C15.1, U1.21 (DVDD), U1.22 (DVDD)
unnamed: C14.1, U1.60 (AVDD)
unnamed: B1.1 (IN), Y1.SIG (SIGNAL)
unnamed: B1.3 (OUT1), C17.1
unnamed: B1.4 (OUT2), C16.1
unnamed: C16.2, U1.8 (RFP)
unnamed: C17.2, U1.9 (RFN)
unnamed: C18.1, Q1.3 (2), U1.57 (XTAL1)
unnamed: C19.1, Q1.1, U1.56 (XTAL2)
unnamed: IC2.1 (STAT), IC3.1 (STAT), LED2.3 (C)
unnamed: BATT2.P, C4.+, IC2.3 (VBAT), S1.2
unnamed: LED1.3 (C), U1.2 (PF3)
RADIO_RX: RADIO1.3
RADIO_TX: RADIO1.2
RESET-CTRL: JP1.7, R9.1, U1.12 (RSTN)
RESET-FLIER: JP1.8, U1.48 (PE2)
RXD0: JP1.1, U1.46 (PE0)
RXD1: U1.27 (PD2), U2.1 (TXD)
SCK: JP1.6, U1.37 (PB1/SCK)
SCL: R5.1, U1.25 (PD0), X11.SCL
SDA: R6.1, U1.26 (PD1), X11.SDA
TXD0: JP1.3, U1.47 (PE1)
TXD1: U1.28 (PD3), U2.5 (RXD)
VBATT: C3.+, IC1.1 (IN), IC1.3 (EN), S1.1
VBATT_CHG: C5.+, IC3.3 (VBAT), JP1.9
VUSB: C6.+, IC2.4 (VDD), IC3.4 (VDD), R2.1, USB.VBUS
